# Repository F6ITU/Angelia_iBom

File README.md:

# Angelia_iBom
Kicad iBom for OpenHPSDR Angelia SDR main board (reversing)

This repository is dedicated to all people wishing to home-built the OpenHPSDR Angelia board. 

This reversing has been done using the official BOM, the original silkmask and the schematic made by the OpenHPSDR group

As most of HPSDR design have been made with a close source EDA (probably Altium), it was necessary to offer an open hardware kind of help 
to the rare and brave people who had the chance to get a grip on a bare Angelia board

This iBom is not fully documented, obvious component placement have been ommited. Feel free to complete the job if you feel yourself 
brave enough 

the 3D picture below gives an idea of the progression

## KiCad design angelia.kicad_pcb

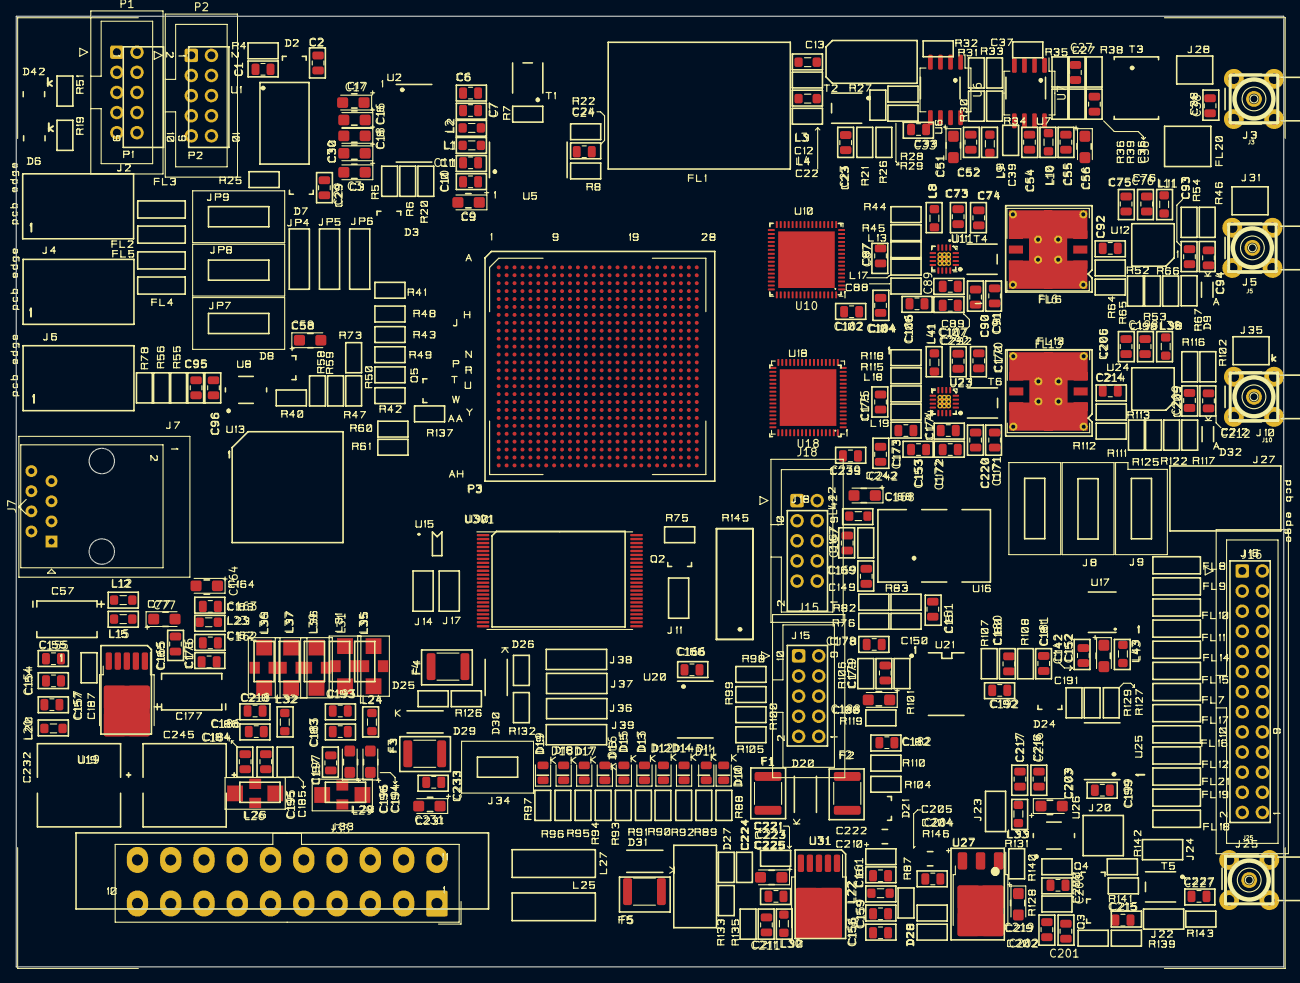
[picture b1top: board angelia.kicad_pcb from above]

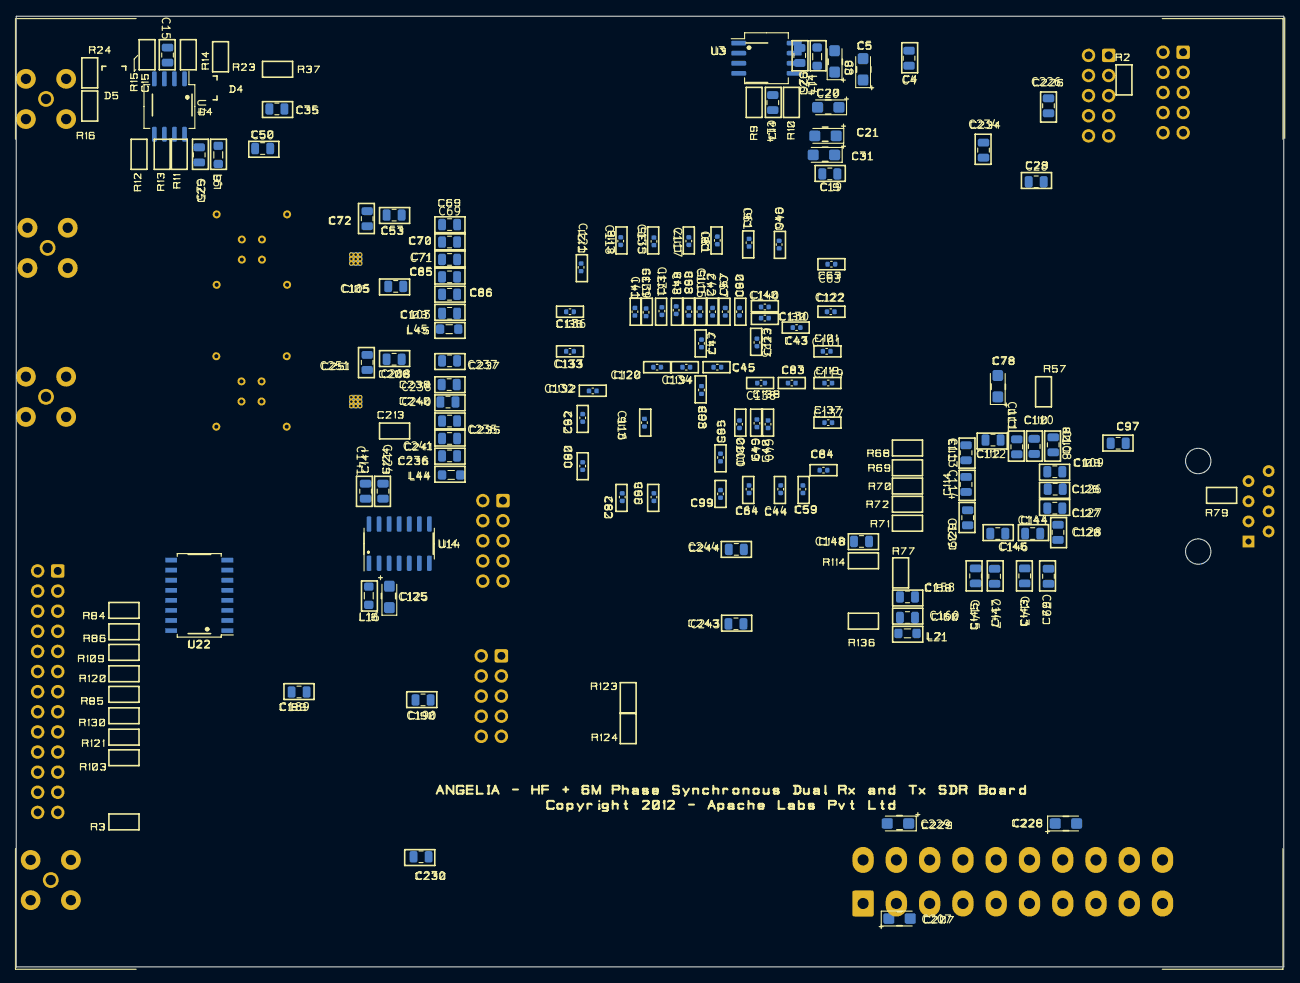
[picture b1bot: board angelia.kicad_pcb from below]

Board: 2 copper layers, 160.0 x 120.0 mm, 301 parts (125 on the bottom side), 15 nets, no tracks yet.

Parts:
C1, C2, C28, C29: 10p; C_0805_2012Metric
C3, C5, C8, C9, C16, C17, C18, C20, C21, C30, C31, C51, C56, C58, C77, C78, C125, C152, C164, C168, C188, C194, C196, C203, C207, C219, C223, C228, C229, C231: 10UF; CP_EIA-3216-18_Kemet-A
C4, C7, C11, C14, C15, C19, C23, C24, C25, C26, C27, C33, C35, C36, C38, C50, C52, C54, C55, C69, C71, C74, C76, C79, C86, C89, C90, C92, C93, C94, C96, C97, C104, C106, C111, C124, C142, C145, C148, C153, C154, C155, C156, C158, C161, C163, C166, C169, C171, C174, C182, C183, C189, C190, C192, C193, C197, C198, C199, C200, C202, C204, C209, C211, C212, C214, C215, C216, C218, C225, C226, C227, C230, C233, C235, C237, C238, C240, C244, C292: 100n; C_0805_2012Metric
C6, C10, C53, C85, C91, C95, C102, C108, C109, C110, C112, C113, C114, C126, C127, C128, C129, C141, C143, C144, C146, C147, C151, C157, C159, C160, C162, C167, C201, C208, C217, C220, C234, C236, C241, C243: 10n; C_0805_2012Metric
C40, C49, C60, C62, C80, C100, C132, C133: 1n; C_0402_1005Metric
C41, C43, C44, C45, C46, C47, C48, C61, C63, C64, C65, C66, C67, C68, C81, C83, C84, C98, C99, C101, C115, C116, C117, C118, C119, C120, C122, C123, C134, C135, C137, C138, C139: 100n; C_0402_1005Metric
C42, C59, C82, C121, C130, C131, C136, C140: 10n; C_0402_1005Metric
C70, C72, C73, C103, C107, C170, C172, C179, C180, C239, C242, C251: 1n; C_0805_2012Metric
C75, C87, C105, C173, C175, C206: 100p; C_0805_2012Metric
C165, C176, C178, C181, C184, C186, C195: 10u; C_0805_2012Metric
D10, D11, D12, D13, D14, D15, D16, D17, D18, D19: LED_Small; LED_0805_2012Metric
F1, F2, F3, F4, F5: Fuse_Small; Fuse_1812_4532Metric
FL6, FL13: RLP-50+; Mini-Circuits_GP1212_LandPatternPL-176
J3, J5, J10, J25: Conn_Coaxial; SMA_PINS
J7: RJ45; RJ45_Amphenol_54602-x08_Horizontal
J15, J18: Conn_02x05_Top_Bottom; IDC-Header_2x05_P2.54mm_Vertical
J16: Conn_02x13_Top_Bottom; IDC-Header_2x13_P2.54mm_Vertical
J33: ATX-20; Molex_Mini-Fit_Jr_5566-20A_2x10_P4.20mm_Vertical
L1, L2, L6, L8, L9, L10, L11, L12, L14, L15, L16, L20, L21, L22, L23, L24, L30, L32, L33, L38, L41, L42, L43, L44, L45: 220; L_0805_2012Metric_Pad1.05x1.20mm_HandSolder
L3: 560nH; L_0805_2012Metric_Pad1.05x1.20mm_HandSolder
L4: 22n; L_0805_2012Metric_Pad1.05x1.20mm_HandSolder
L26, L29, L31, L35, L36, L37, L39: FerriteBead_Small; Ferrite_LC_NFM41P
P1, P2: Conn_02x05_Top_Bottom; IDC-Header_2x05_P2.54mm_Vertical
P3: EP4CE115F780; BGA-676_27.0x27.0mm_Layout26x26_P1.0mm_Ball0.6mm_Pad0.5mm_N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
U3, U4: LMC6482AM; SO-8_5.3x6.2mm_P1.27mm
U6, U7: OPA2674IC; SO-8_5.3x6.2mm_P1.27mm
U10, U18: LTC2208xUP; QFN-64-1EP_9x9mm_P0.5mm_EP7.15x7.15mm
U11, U23: LTC6400; QFN-16-1EP_3x3mm_P0.5mm_EP1.7x1.7mm_ThermalVias
U14: SN65LVDM180D; SOIC-14_3.9x8.7mm_P1.27mm
U19, U31: TO-252-5; TO-252-5_TabPin3
U22: ULN2003A; SOIC-16W_5.3x10.2mm_P1.27mm
U27: TO-252-3; TO-252-3_TabPin2
U301: TSOP-I-48_18.4x12mm_P0.5mm

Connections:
unnamed: J33.1 (+3.3V), J33.2 (+3.3V), J33.11 (+3.3V)
unnamed: J33.4 (+5V), J33.6 (+5V), J33.19 (+5V), J33.20 (+5V)
unnamed: J33.3 (GND), J33.5 (GND), J33.7 (GND), J33.13 (GND), J33.15 (GND), J33.16 (GND), J33.17 (GND)
unnamed: U10.17 (GND), U10.64 (GND), U10.65 (GND)
unnamed: U10.31 (OGND), U10.50 (OGND)
unnamed: U10.3 (REFHA), U10.4 (REFHA)
unnamed: U10.13 (REFHB), U10.14 (REFHB)
unnamed: U10.5 (REFLA), U10.6 (REFLA)
unnamed: U10.11 (REFLB), U10.12 (REFLB)
unnamed: U18.17 (GND), U18.64 (GND), U18.65 (GND)
unnamed: U18.31 (OGND), U18.50 (OGND)
unnamed: U18.3 (REFHA), U18.4 (REFHA)
unnamed: U18.13 (REFHB), U18.14 (REFHB)
unnamed: U18.5 (REFLA), U18.6 (REFLA)
unnamed: U18.11 (REFLB), U18.12 (REFLB)

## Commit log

2023-06-10 first commit, decoupling caps ok
2023-06-10 screen capture added in readme
2023-06-10 all decoupling done
2023-06-11 beginning special components
2023-06-11 some more caps, still some more caps and RJ45
2023-06-12 ferrites and vlsi
2023-06-13 ferrites and lna
2023-06-13 more vlsi, more inductances
2023-06-13 new 3D pic
2023-06-13 all mlcc are done
2023-06-13 most pull-up resistor done
2023-06-14 botom side completed
2023-06-14 all resistors are not futile
2023-06-14 that's all folks
2023-06-14 final release
2023-06-17 new readme
